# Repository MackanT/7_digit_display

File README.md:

# 7_digit_display
Code for a 7 digit display using 3 WS2812b per segment

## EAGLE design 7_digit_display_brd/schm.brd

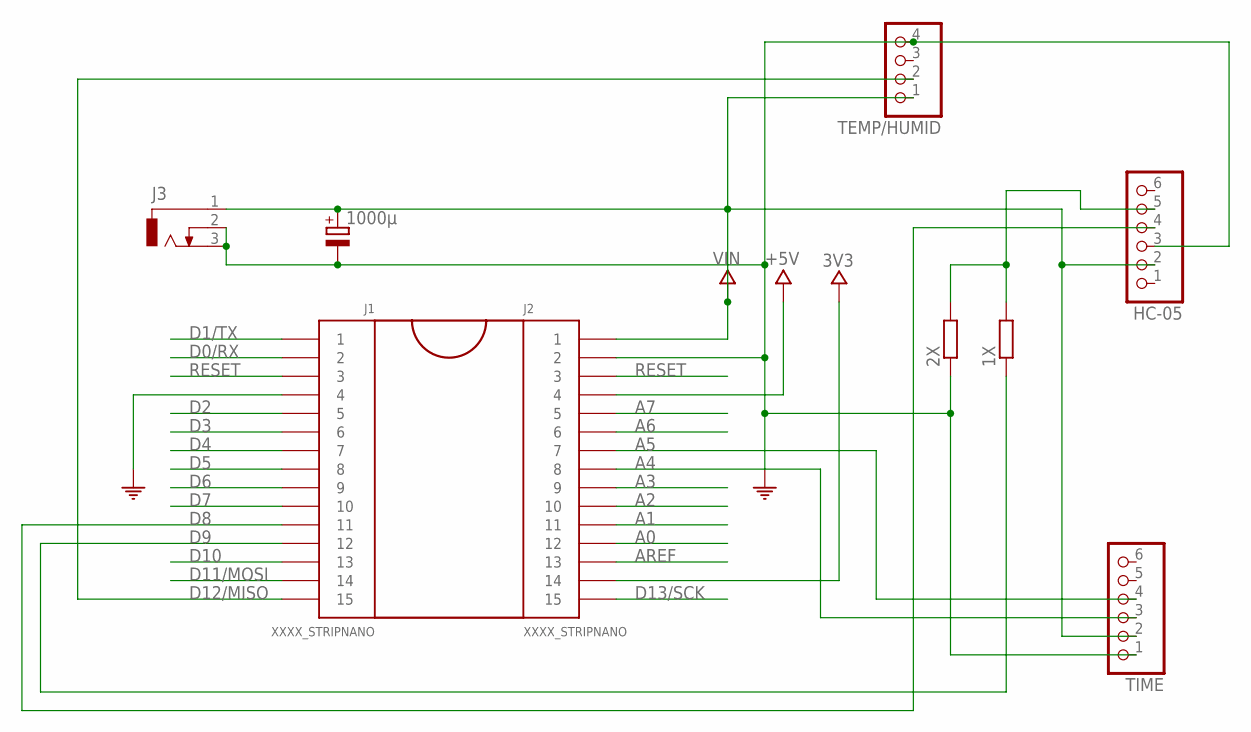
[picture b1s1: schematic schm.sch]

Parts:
1X, 2X: R-EU_0207/10; 0207/10
1000μ: CPOL-EUE3.5-10; E3,5-10
HC-05: PINHD-1X6/90; 1X06/90
J1, J2: XXXX_STRIPNANO; HEAD15-NOSS
J3: DCJ0303
TEMP/HUMID: PINHD-1X4; 1X04
TIME: PINHD-1X6/90; 1X06/90

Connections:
3V3: J2.14
+5V: J2.4
A0: J2.12
A1: J2.11
A2: J2.10
A3: J2.9
A4: J2.8, TIME.3
A5: J2.7, TIME.4
A6: J2.6
A7: J2.5
AREF: J2.13
COM: 2X.1, 1000μ.-, HC-05.3, J1.4, J2.2, J3.2, J3.3, TEMP/HUMID.4, TIME.1
D0/RX: J1.2
D1/TX: J1.1
D2: J1.5
D3: J1.6
D4: J1.7
D5: J1.8
D6: J1.9
D7: J1.10
D8: HC-05.4, J1.11
D9: 1X.1, J1.12
D10: J1.13
D11/MOSI: J1.14
D12/MISO: J1.15, TEMP/HUMID.2
D13/SCK: J2.15
unnamed: 1X.2, 2X.2, HC-05.5
RESET: J1.3, J2.3
VIN: 1000μ.+, HC-05.2, J2.1, J3.1, TEMP/HUMID.1, TIME.2

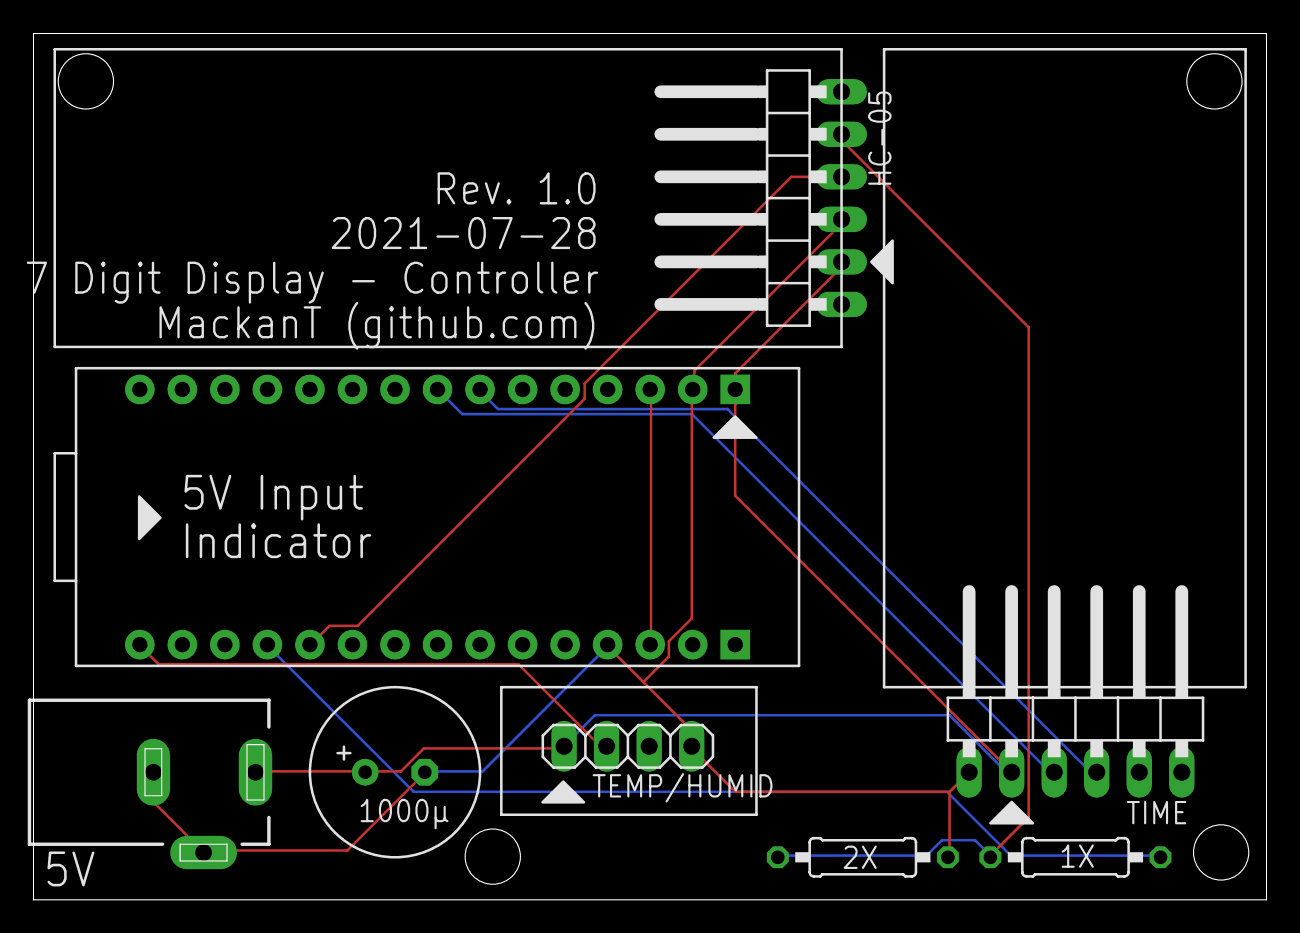
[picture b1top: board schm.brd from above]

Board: 2 copper layers, 73.6 x 51.7 mm, 9 parts (0 on the bottom side), 9 nets.

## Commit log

2021-06-27 Initial working code
2021-08-02 Finished edition #1
2021-08-02 Prototype board #1
2021-10-28 Working version 2.0
2022-06-02 Updated w. Date compatability
2022-06-03 V1 BT app
